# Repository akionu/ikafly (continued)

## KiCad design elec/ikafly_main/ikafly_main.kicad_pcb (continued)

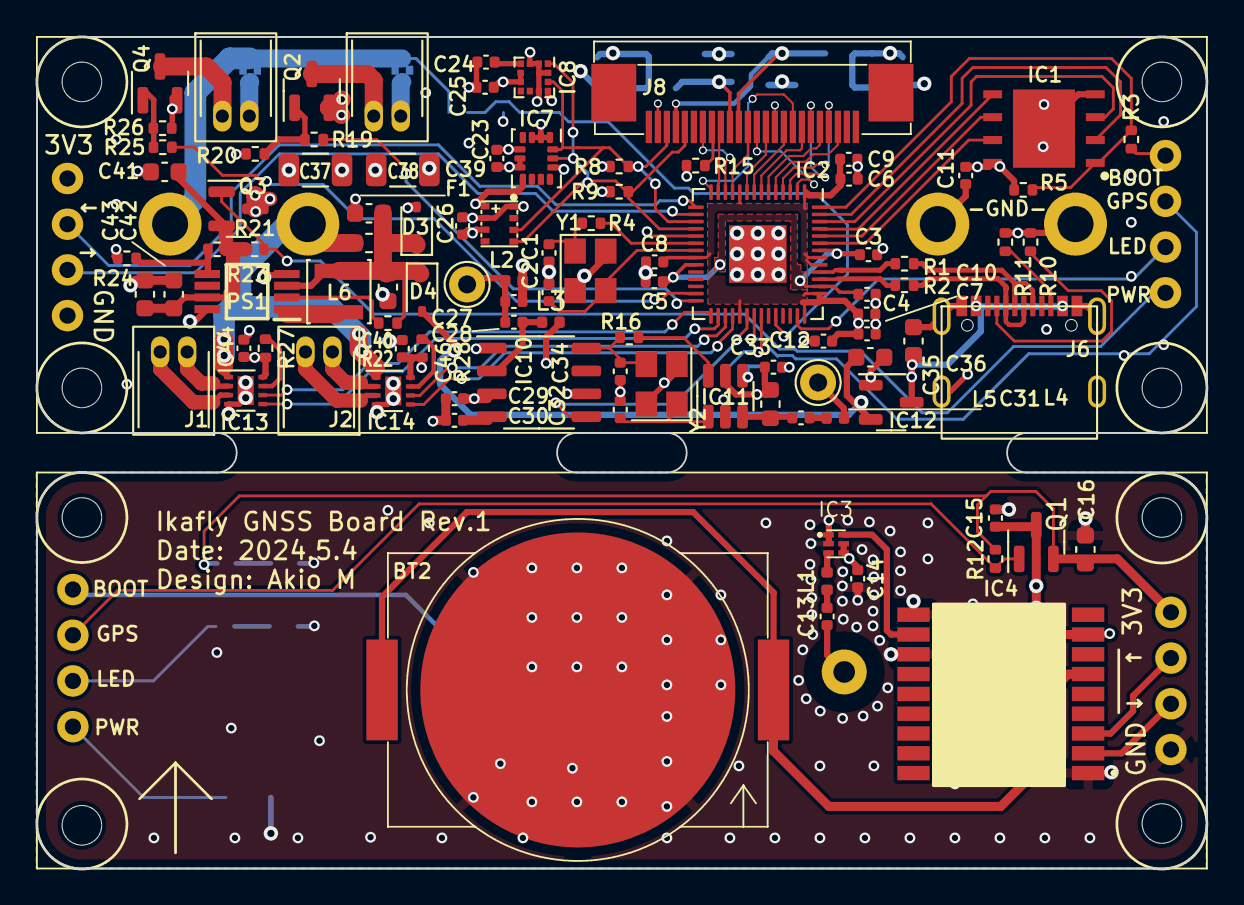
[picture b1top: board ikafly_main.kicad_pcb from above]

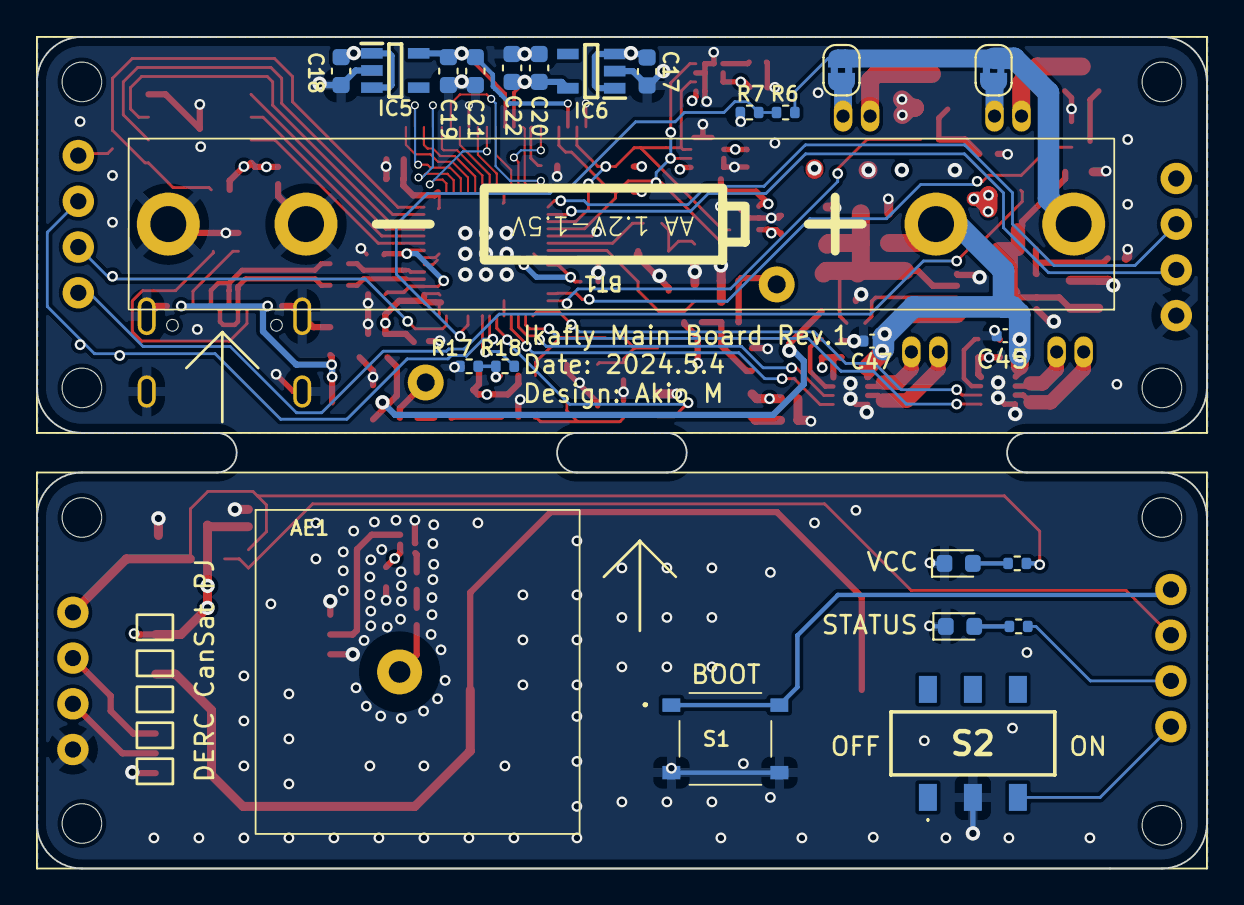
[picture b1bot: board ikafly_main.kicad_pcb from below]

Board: 4 copper layers, 65.0 x 46.2 mm, 132 parts (25 on the bottom side), 89 nets.

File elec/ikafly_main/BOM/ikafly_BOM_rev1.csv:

"Reference","Value","Datasheet","Footprint","Qty","DNP"
"AE1","ANT_GNSS","~","Ikafly_lib:BWGNSCNX18-18W2","1",""
"AE2,AE3","ANT_315MHz","~","Connector_Pin:Pin_D1.0mm_L10.0mm","2",""
"BT1","AA_Cell","~","Ikafly_lib:Conn_MY-AA","1",""
"BT2","CR2032","~","Ikafly_lib:MY-2032-08-J-Fe","1",""
"C1,C2,C31,C32,C34","20p","~","Capacitor_SMD:C_0402_1005Metric","5",""
"C3,C6","1u","~","Capacitor_SMD:C_0402_1005Metric","2",""
"C4,C5,C7,C8,C9,C10,C11,C12,C14,C15,C23,C24,C25,C26,C29,C44,C45,C46,C47","100n","~","Capacitor_SMD:C_0402_1005Metric","19",""
"C13","470p","~","Capacitor_SMD:C_0402_1005Metric","1",""
"C16,C17,C18,C19,C20,C21,C22,C35,C36","10u","~","Capacitor_SMD:C_0603_1608Metric","9",""
"C27","6.8p","~","Capacitor_SMD:C_0402_1005Metric","1",""
"C28","1.5p","~","Capacitor_SMD:C_0402_1005Metric","1",""
"C30","0.47u","~","Capacitor_SMD:C_0402_1005Metric","1",""
"C33","2.2u","~","Capacitor_SMD:C_0402_1005Metric","1",""
"C37,C38","100u","~","Capacitor_SMD:C_1206_3216Metric","2",""
"C39,C40,C41,C42,C43","22u","~","Capacitor_SMD:C_0603_1608Metric","5",""
"D1,D2","LED","~","LED_SMD:LED_0603_1608Metric","2",""
"D3,D4","CUS10S30","~","Diode_SMD:D_SOD-323","2",""
"F1","Polyfuse","~","Fuse:Fuse_0603_1608Metric","1",""
"H1,H2,H3,H4,H5,H6,H7,H8","MountingHole","~","MountingHole:MountingHole_2.2mm_M2","8",""
"IC1","W25Q32JVZPIQ","https://www.winbond.com/hq/search-resource-file.jsp?partNo=W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","SamacSys_Parts:SON127P600X500X80-9N-D","1",""
"IC2","RP2040","https://datasheets.raspberrypi.com/rp2040/rp2040-datasheet.pdf","Package_DFN_QFN:QFN-56-1EP_7x7mm_P0.4mm_EP3.2x3.2mm","1",""
"IC3","AT2659","","Ikafly_lib:AT2659","1",""
"IC4","ATGM336H-5N31","https://datasheet.lcsc.com/szlcsc/ZHONGKEWEI-ATGM336H-5N31_C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","SamacSys_Parts:ATGM336H5N31","1",""
"IC5","ME6211C28M5G-N ","","SamacSys_Parts:SOT95P282X145-5N","1",""
"IC6","ME6211C12M5G-N ","","SamacSys_Parts:SOT95P282X145-5N","1",""
"IC7","LSM6DS3TR-C","http://www.st.com/resource/en/datasheet/lsm6ds3tr-c.pdf","Package_LGA:LGA-14_3x2.5mm_P0.5mm_LayoutBorder3x4y","1",""
"IC8","LIS3MDLTR","","Package_LGA:LGA-12_2x2mm_P0.5mm","1",""
"IC9","SPL06-001","","Ikafly_lib:Goertek_SPL06-001","1",""
"IC10","WF490RE","","Package_SO:SOP-8_3.9x4.9mm_P1.27mm","1",""
"IC11","WF4455TD","","Package_TO_SOT_SMD:SOT-23-6","1",""
"IC12","XC6206P182MR","https://www.torexsemi.com/file/xc6206/XC6206.pdf","Package_TO_SOT_SMD:SOT-23-3","1",""
"IC13,IC14","DRV8837","http://www.ti.com/lit/ds/symlink/drv8837.pdf","Package_SON:WSON-8-1EP_2x2mm_P0.5mm_EP0.9x1.6mm","2",""
"J1,J2","Motor_Conn","~","Ikafly_lib:JST_ZH_2_Side","2",""
"J3,J4","Nichrome_Conn","~","Ikafly_lib:JST_ZH_2_Side","2",""
"J5,J7","GPS2MCU","~","Ikafly_lib:GPS2MCU_Conn","2",""
"J6","USB_type_C","","Ikafly_lib:USB_type_C","1",""
"J8","OV2640_FPC_P0.5_24P","","Ikafly_lib:FC05-SXXDCU-00","1",""
"JP1,JP2","Jumper_2_Bridged","~","Jumper:SolderJumper-2_P1.3mm_Bridged2Bar_RoundedPad1.0x1.5mm","2",""
"L1","6.8nH","https://www.lcsc.com/datasheet/lcsc_datasheet_2302231208_FH-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","Inductor_SMD:L_0402_1005Metric","1",""
"L2","39nH","~","Inductor_SMD:L_0402_1005Metric","1",""
"L3","68nH","~","Inductor_SMD:L_0402_1005Metric","1",""
"L4","33nH","~","Inductor_SMD:L_0402_1005Metric","1",""
"L5","3.3uH","https://www.lcsc.com/datasheet/lcsc_datasheet_2305191017_HYH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","Inductor_SMD:L_0603_1608Metric","1",""
"L6","1.5uH","~","Inductor_SMD:L_Sunlord_SWPA3015S","1",""
"PS1","PAM2401SCADJ","https://www.diodes.com/assets/Datasheets/PAM2401.pdf","SamacSys_Parts:SOP65P490X110-8N","1",""
"Q1,Q3","CJ2301-ES","https://www.infineon.com/dgdl/irlml6402pbf.pdf?fileId=5546d4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","Package_TO_SOT_SMD:SOT-23","2",""
"Q2,Q4","Q_NMOS_GSD","~","Package_TO_SOT_SMD:SOT-23","2",""
"R1,R2","27","~","Resistor_SMD:R_0402_1005Metric","2",""
"R3,R4,R6,R16,R19,R25","1k","~","Resistor_SMD:R_0402_1005Metric","6",""
"R5,R13,R14,R15,R18,R20,R22,R26,R27,R28","10k","~","Resistor_SMD:R_0402_1005Metric","10",""
"R7","DNF","~","Resistor_SMD:R_0402_1005Metric","1",""
"R8,R9","2.2k","~","Resistor_SMD:R_0402_1005Metric","2",""
"R10,R11","5.1k","~","Resistor_SMD:R_0402_1005Metric","2",""
"R12,R17,R21","100k","~","Resistor_SMD:R_0402_1005Metric","3",""
"R23","680k","~","Resistor_SMD:R_0402_1005Metric","1",""
"R24","150k","~","Resistor_SMD:R_0402_1005Metric","1",""
"S1","TS-1187A-B-A-B","http://www.helloxkb.com/public/images/pdf/TS-1187A-X-X-X.pdf","SamacSys_Parts:TS1187ABAB","1",""
"S2","MST22D18G2_125","https://datasheet.lcsc.com/lcsc/2110190930_SHOU-HAN-MST22D18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","SamacSys_Parts:MST22D18G2125","1",""
"Y1","Crystal_12MHz","~","Crystal:Crystal_SMD_3225-4Pin_3.2x2.5mm","1",""
"Y2","9.844MHz","~","Crystal:Crystal_SMD_3225-4Pin_3.2x2.5mm","1",""

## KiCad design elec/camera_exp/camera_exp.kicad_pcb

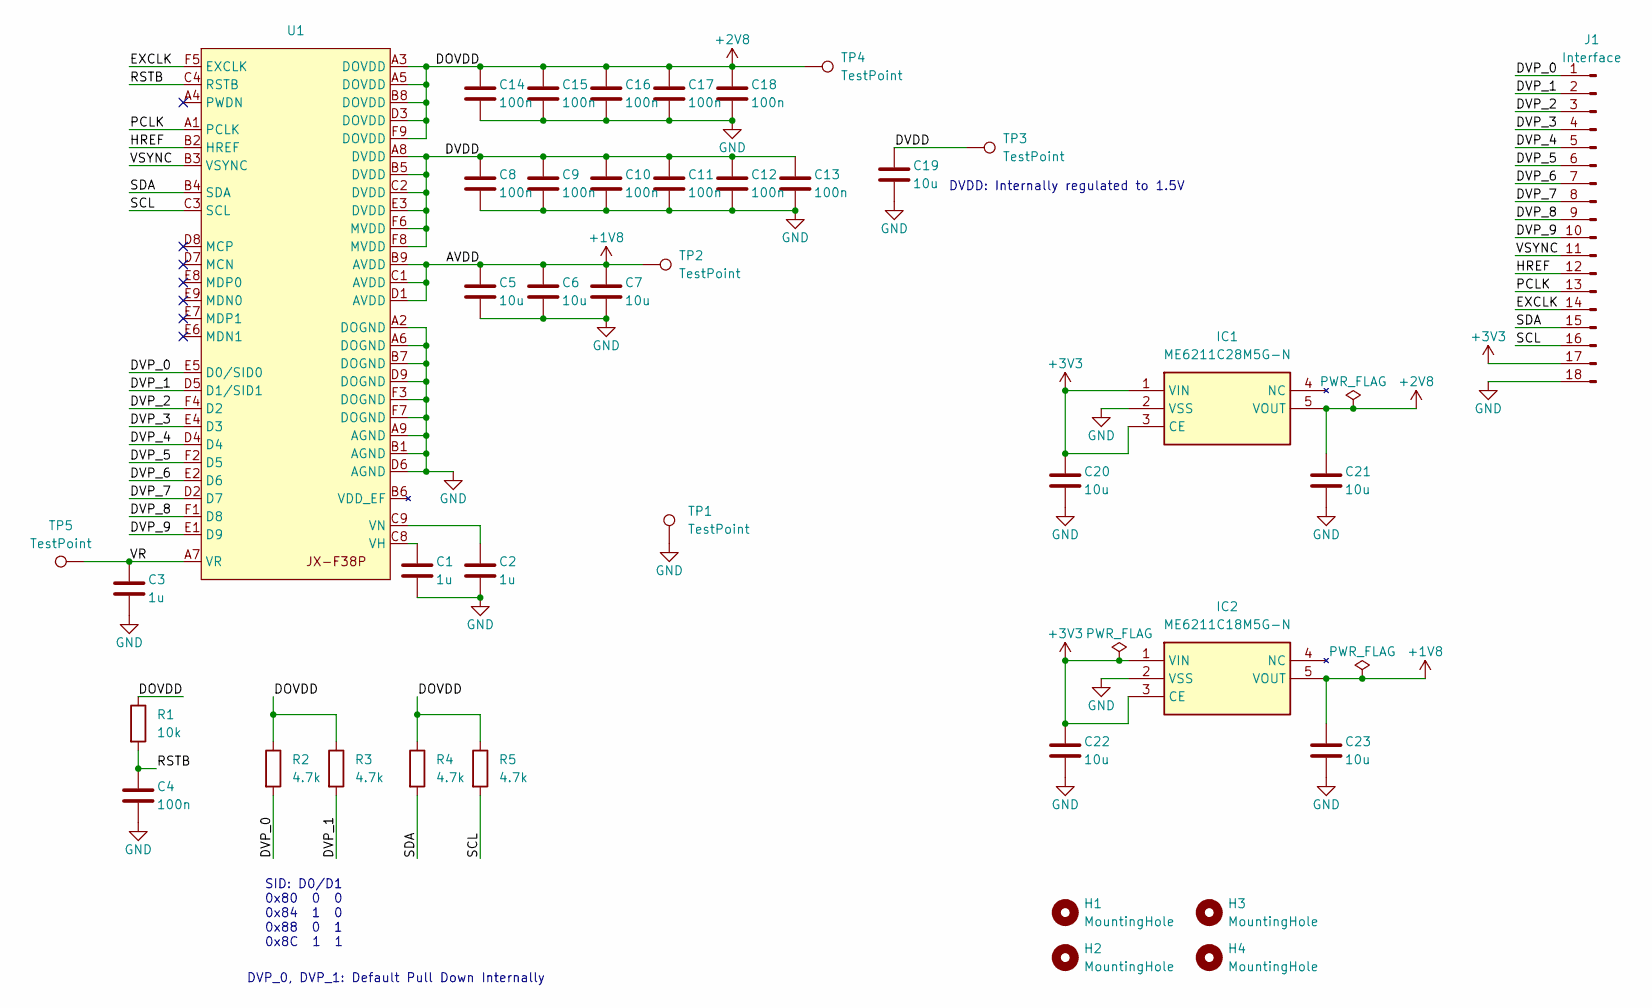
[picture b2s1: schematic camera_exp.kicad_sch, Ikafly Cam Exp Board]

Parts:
C1, C2, C3: 1u; C_0402_1005Metric
C4, C8, C9, C10, C11, C12, C13, C14, C15, C16, C17, C18: 100n; C_0402_1005Metric
C5, C6, C7, C19, C20, C21, C22, C23: 10u; C_0402_1005Metric
H1, H2, H3, H4: MountingHole; MountingHole_2.2mm_M2
IC1: ME6211C28M5G-N; SOT95P282X145-5N; Manufacturer_Part_Number ME6211C33M5G
IC2: ME6211C18M5G-N; SOT95P282X145-5N; Manufacturer_Part_Number ME6211C33M5G
J1: Interface; PinHeader_2x09_P2.54mm_Vertical
R1: 10k; R_0402_1005Metric
R2, R3, R4, R5: 4.7k; R_0402_1005Metric
TP1, TP2, TP3, TP4, TP5: TestPoint; TestPoint_Pad_D1.0mm
U1: JX-F38P

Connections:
+1V8: C5.1, C6.1, C7.1, C23.1, IC2.5 (VOUT), TP2.1, U1.B9 (AVDD), U1.C1 (AVDD), U1.D1 (AVDD)
+2V8: C14.1, C15.1, C16.1, C17.1, C18.1, C21.1, IC1.5 (VOUT), R1.1, R2.1, R3.1, R4.1, R5.1, TP4.1, U1.A3 (DOVDD), U1.A5 (DOVDD), U1.B8 (DOVDD), U1.D3 (DOVDD), U1.F9 (DOVDD)
+3V3: C20.1, C22.1, IC1.1 (VIN), IC1.3 (CE), IC2.1 (VIN), IC2.3 (CE), J1.17
/DVDD: C8.1, C9.1, C10.1, C11.1, C12.1, C13.1, C19.1, TP3.1, U1.A8 (DVDD), U1.B5 (DVDD), U1.C2 (DVDD), U1.E3 (DVDD), U1.F6 (MVDD), U1.F8 (MVDD)
/DVP_0: J1.1, R2.2, U1.E5 (D0/SID0)
/DVP_1: J1.2, R3.2, U1.D5 (D1/SID1)
/DVP_2: J1.3, U1.F4 (D2)
/DVP_3: J1.4, U1.E4 (D3)
/DVP_4: J1.5, U1.D4
/DVP_5: J1.6, U1.F2 (D5)
/DVP_6: J1.7, U1.E2 (D6)
/DVP_7: J1.8, U1.D2 (D7)
/DVP_8: J1.9, U1.F1 (D8)
/DVP_9: J1.10, U1.E1 (D9)
/EXCLK: J1.14, U1.F5 (EXCLK)
/HREF: J1.12, U1.B2 (HREF)
/MCN: U1.D7 (MCN)
/MCP: U1.D8 (MCP)
/MDN0: U1.E9 (MDN0)
/MDN1: U1.E6 (MDN1)
/MDP0: U1.E8 (MDP0)
/MDP1: U1.E7 (MDP1)
/PCLK: J1.13, U1.A1 (PCLK)
/PWDN: U1.A4 (PWDN)
/RSTB: C4.1, R1.2, U1.C4 (RSTB)
/SCL: J1.16, R5.2, U1.C3 (SCL)
/SDA: J1.15, R4.2, U1.B4 (SDA)
/VR: C3.1, TP5.1, U1.A7 (VR)
/VSYNC: J1.11, U1.B3 (VSYNC)
GND: C1.2, C2.2, C3.2, C4.2, C5.2, C6.2, C7.2, C8.2, C9.2, C10.2, C11.2, C12.2, C13.2, C14.2, C15.2, C16.2, C17.2, C18.2, C19.2, C20.2, C21.2, C22.2, C23.2, IC1.2 (VSS), IC2.2 (VSS), J1.18, TP1.1, U1.A2 (DOGND), U1.A6 (DOGND), U1.A9 (AGND), U1.B1 (AGND), U1.B7 (DOGND), U1.D6 (AGND), U1.D9 (DOGND), U1.F3 (DOGND), U1.F7 (DOGND)
unnamed: C1.1, U1.C8 (VH)
unnamed: C2.1, U1.C9 (VN)

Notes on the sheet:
DVP_0, DVP_1: Default Pull Down Internally
DVDD: Internally regulated to 1.5V
SID: D0/D1 0x80 0 0 0x84 1 0 0x88 0 1 0x8C 1 1

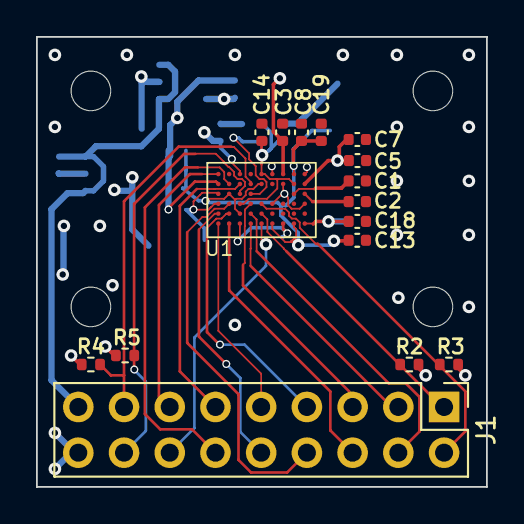
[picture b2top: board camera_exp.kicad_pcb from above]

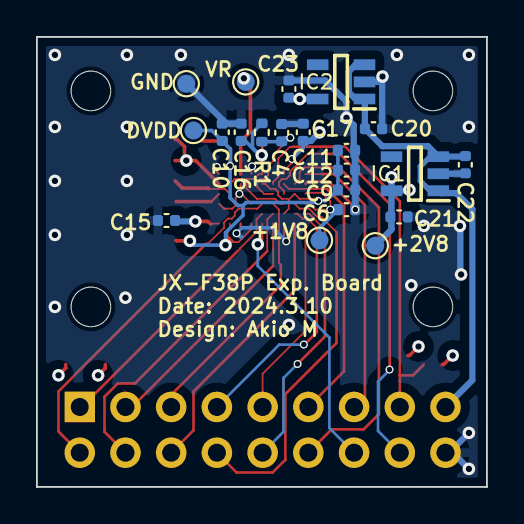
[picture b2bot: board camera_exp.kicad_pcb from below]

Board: 4 copper layers, 25.0 x 25.0 mm, 41 parts (21 on the bottom side), 25 nets.

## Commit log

2024-03-12 intial commit
2024-03-12 mcu board
2024-03-16 update AW
2024-03-17 update pcb
2024-03-18 done rev0a
2024-04-07 add lis3mdl low-level library
2024-04-07 update gitignore
2024-04-09 trying to make camera work
2024-04-13 done cam exp
2024-04-13 add machinery exp
2024-04-26 add exp tire
2024-04-30 working on FM
2024-05-04 update pcb for FM
2024-05-05 done FM PCB
2024-05-09 add lib (press, motor)
2024-05-09 add t-shirts
2024-05-14 certain success in imu
2024-05-15 FreeRTOS
2024-05-16 use freertos to control imu&press simultaneously
2024-05-20 freertos exp
2024-05-21 add freertos
2024-05-21 repair stashed changes
2024-05-24 add cam lib
2024-05-27 add selftest
2024-05-28 add nichrome test
2024-05-28 doing r
2024-05-30 mag calibration
2024-05-30 to build calibration
2024-05-30 git start
2024-05-31 rf works!
2024-06-02 remove unused files
2024-06-05 change cam lib buffer
2024-06-05 change camera buffersize 3->5
2024-06-07 add 予備審査書
2024-06-10 anything is incomplete
2024-06-10 calc distance between goal and ikafly
2024-06-12 get euler
2024-06-14 devide flight
2024-06-14 we can make ikafly comunicate with other one littl
2024-06-15 littlefs does not work
2024-06-15 fix err
2024-06-15 fix mag==0 when didnot calibrated
2024-06-18 communication with other ikafly
2024-06-18 amendment
2024-06-18 amend landing
2024-06-20 using vTaskDelayUntil
2024-06-20 can use imu
2024-06-20 error vTaskCoreAffinitySet
2024-06-20 better freertos config
2024-06-20 update freertos kernel
2024-06-20 argument miss
2024-06-20 remove littlefs
2024-06-20 update freertos config
2024-06-20 add flash exp
2024-06-22 exp. forsafe access to flash
2024-06-23 done: write part of logging
2024-06-25 tabun misu
2024-06-25 not done
2024-06-25 ikafly can calculate direction for goal
2024-06-27 ktkr??
2024-06-28 i didn't know that flash need to ERASE A WHOLE SECTOR before write just A PAGE... orz
2024-06-28 flash try
2024-06-28 bit calculation
2024-06-29 add littlefs
2024-06-29 remove spiffs
2024-06-29 add littlefs log
2024-07-01 add accel log & fix logging err
2024-07-01 fix indent
2024-07-01 add accel log
2024-07-01 fix CMakeList
2024-07-01 add 振動試験の諸元
2024-07-14 add tjpg lib & example
2024-07-14 add count in tjpg
2024-07-15 I can not initialize filesystem again
2024-07-18 fix imu bug
2024-07-18 test
2024-07-18 SINGLE COREgit add -A
2024-07-27 add gomu_guide_tumayouji
2024-07-27 kouzou
2024-07-28 before using event group
2024-07-29 can move
2024-08-01 for E2E I discard fkight2
2024-08-01 some fix
2024-08-01 make cmake like
2024-08-04 itiou done
2024-08-07 update lib
2024-08-07 add angle
2024-08-07 amendment gnss
2024-08-07 distance
2024-08-07 befor change flight
2024-08-08 imu ga okasii
2024-08-08 done ca
2024-08-14 update for flight
2024-10-26 add log
2024-12-06 add machi
